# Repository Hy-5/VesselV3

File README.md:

# Vessel (rev 1.0)

*ISO-FR 75-ish keyboard with I2C OLED, RGB (WS2812B-2020) and rotary encoder*

* Keyboard Maintainer: [Hy-5 (Ismael Coulibaly)](https://github.com/Hy-5)
* Hardware Supported: *STM32F446RET6TR*

[WIP]

Make example for this keyboard (after setting up your build environment):

    qmk compile -kb vessel -km base 2>&1 | ts '%Y-%m-%d %H:%M:%S

Flashing example for this keyboard:

    A - Initial flashing
        1 - Bridge "boot0 to 3v3_1" solder jumper to pull boot0 high
        2 - Desolder logic level shifter to keep boot1 pin low
        3 - Plug in the keyboard, it will boot in dfu bootloader mode
        4 - Use whatever program you prefer, QMK Toolbox, STM32 Programmer, STLink V2 etc.
    B - After initial flashing
        1 - Keep M12 button (row0, col11) pressed while plugging in the keyboard to launch in bootloader mode
        2 - Use QMK Toolbox for flashing

See the [build environment setup](https://docs.qmk.fm/#/getting_started_build_tools) and the [make instructions](https://docs.qmk.fm/#/getting_started_make_guide) for more information. Brand new to QMK? Start with our [Complete Newbs Guide](https://docs.qmk.fm/#/newbs).

## Bootloader

Enter the bootloader in 1 way:

* **Bootmagic reset**: Hold down the M12 key at ((row0, col11) in the matrix) and plug in the keyboard

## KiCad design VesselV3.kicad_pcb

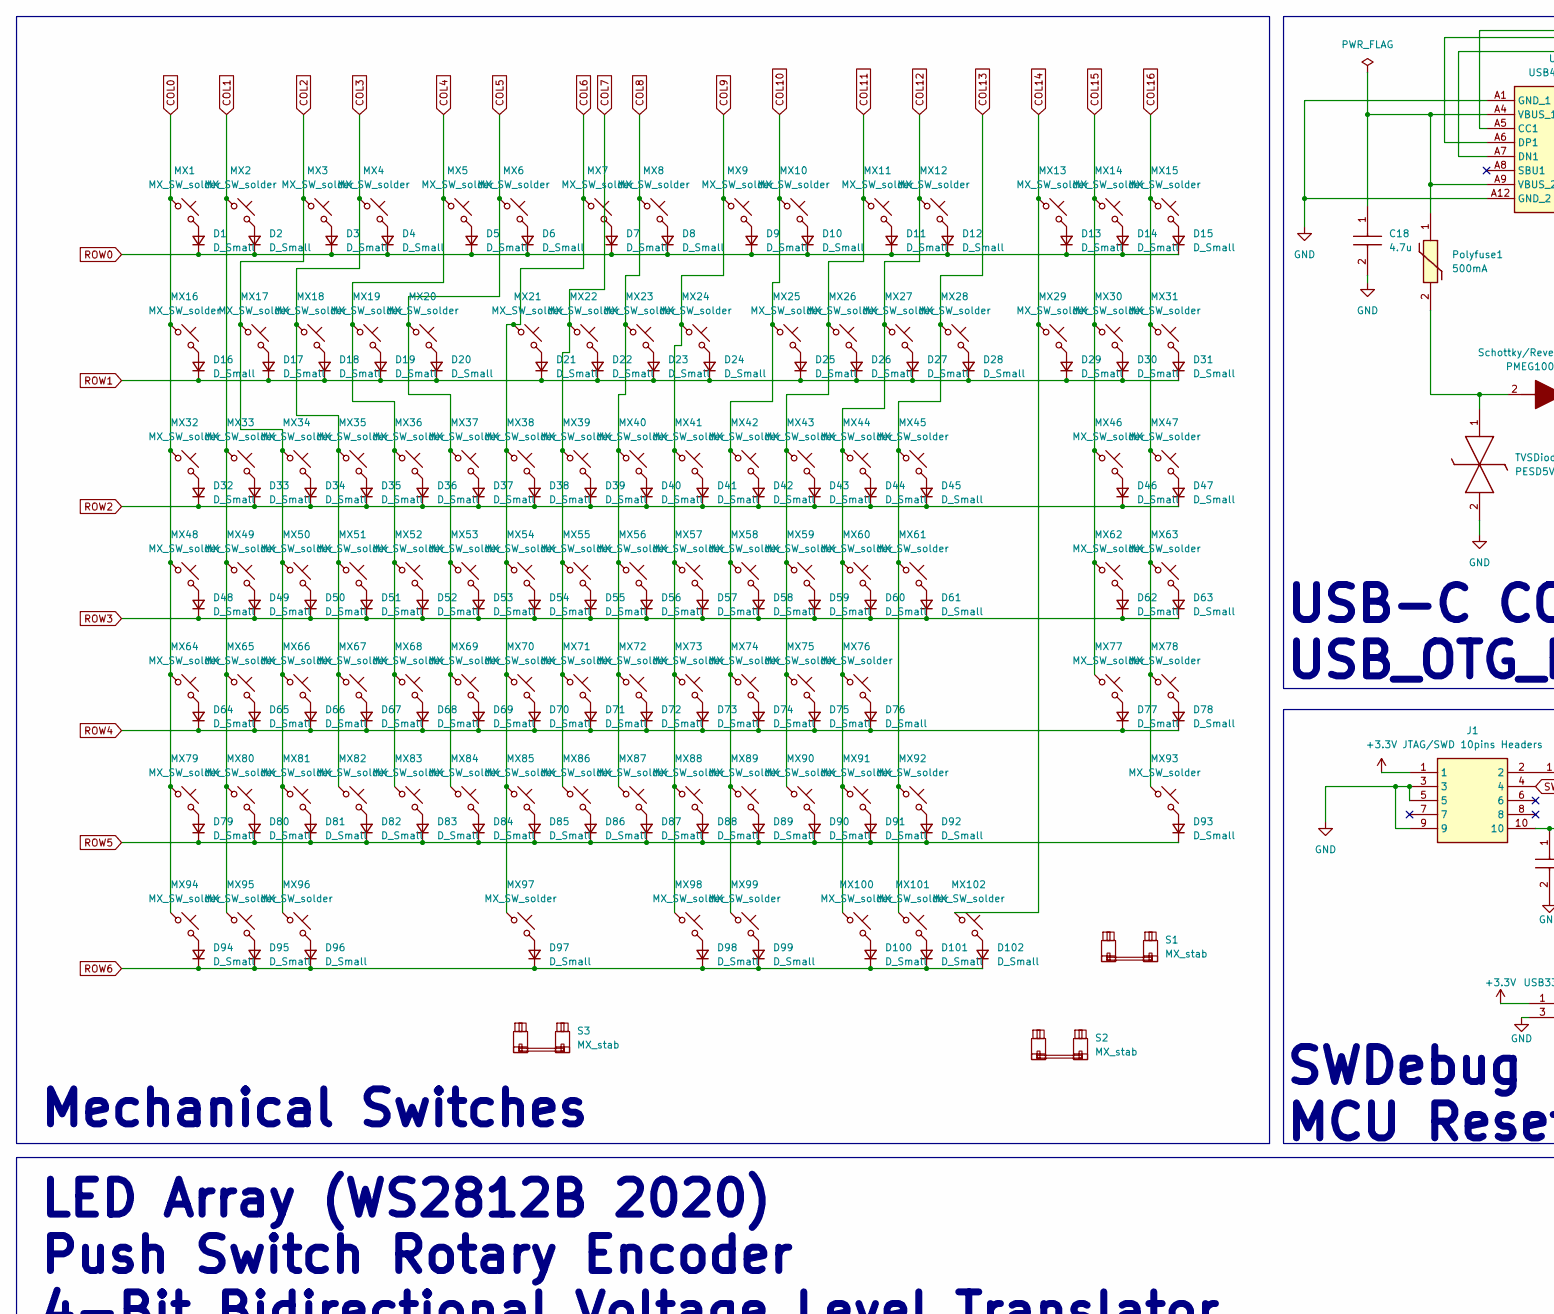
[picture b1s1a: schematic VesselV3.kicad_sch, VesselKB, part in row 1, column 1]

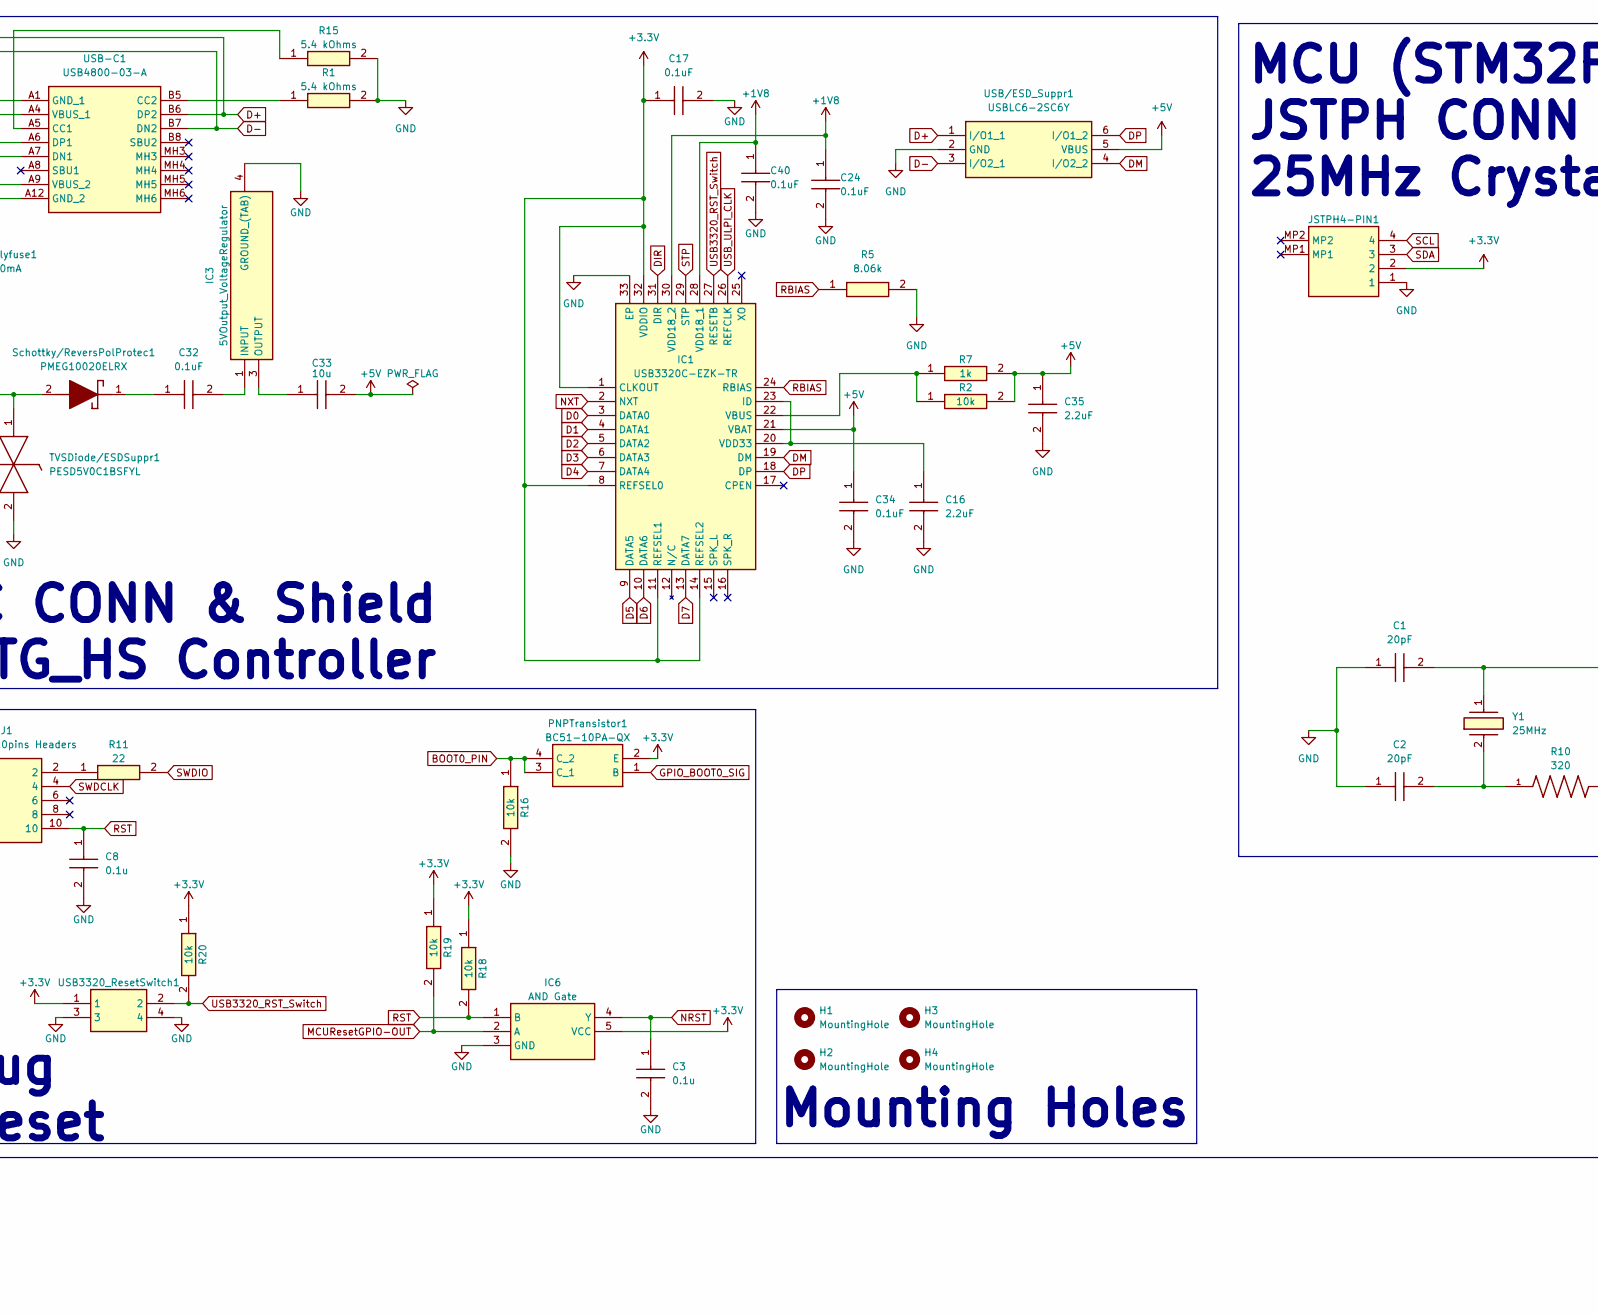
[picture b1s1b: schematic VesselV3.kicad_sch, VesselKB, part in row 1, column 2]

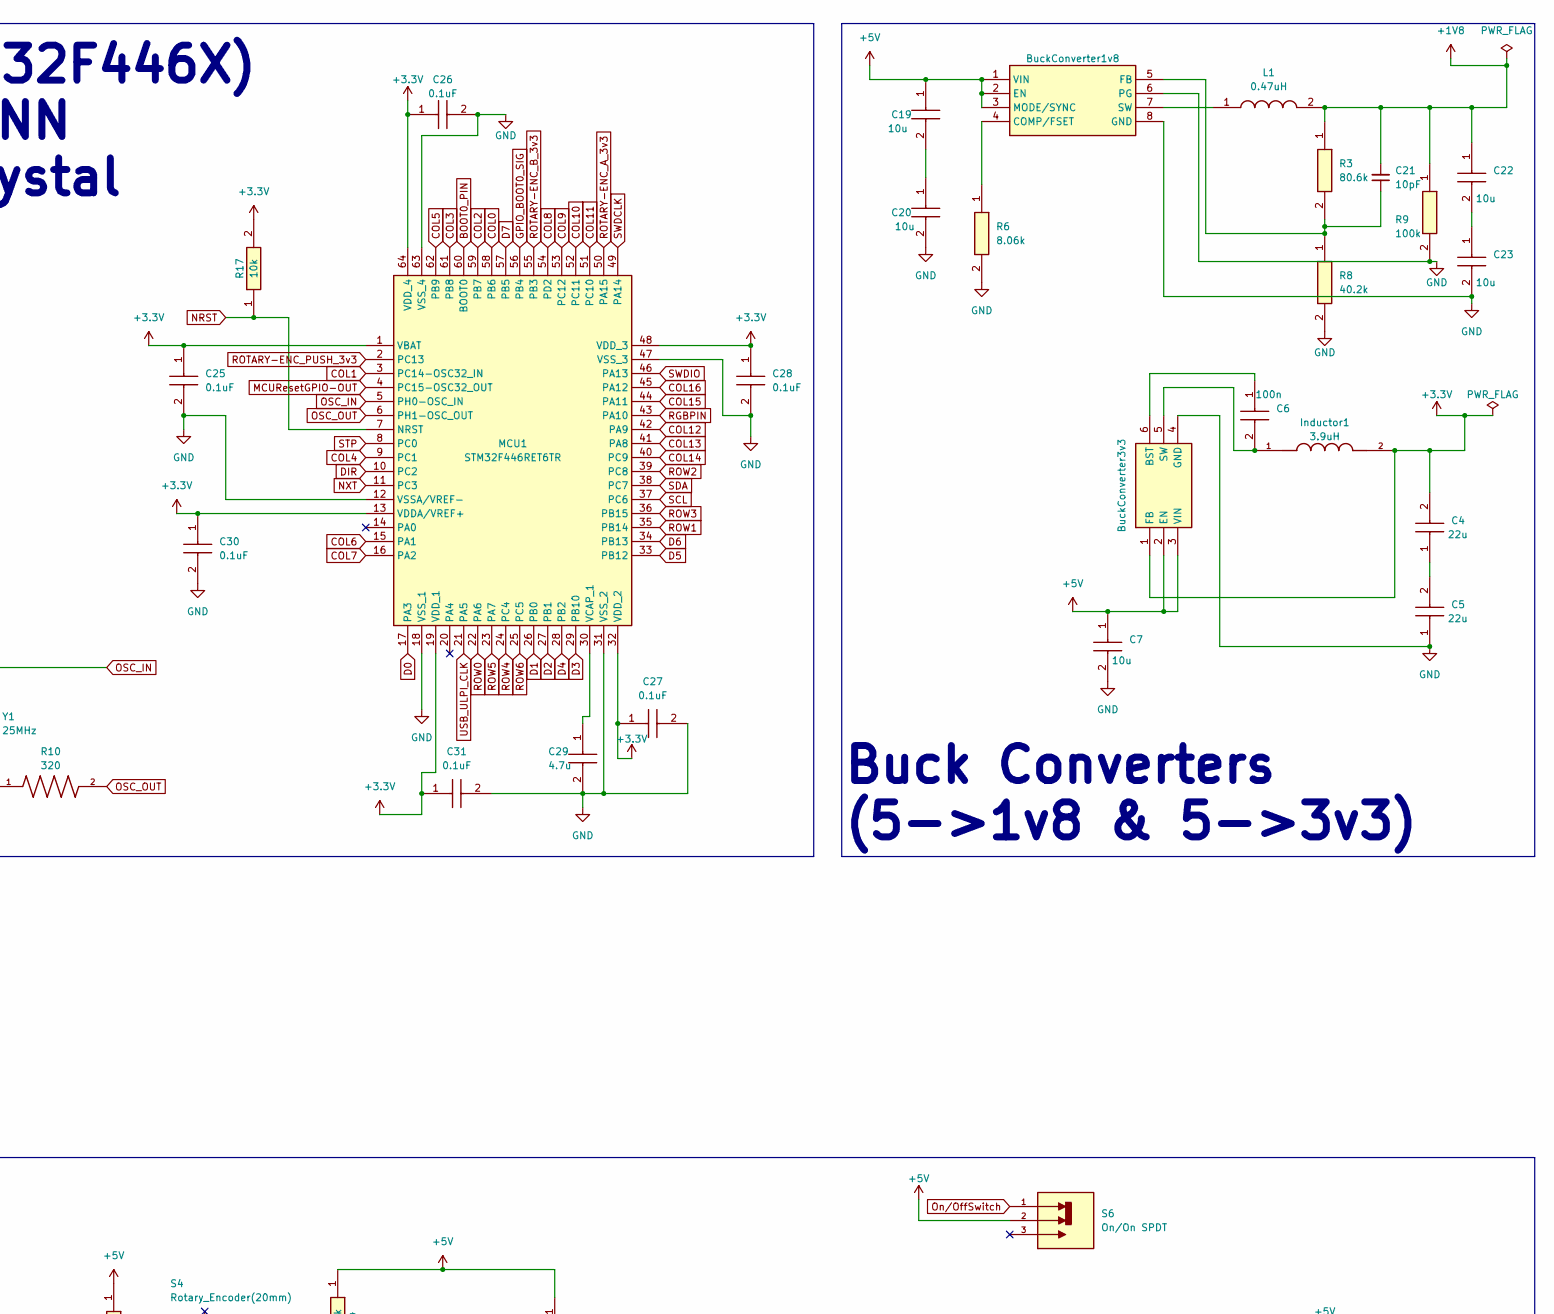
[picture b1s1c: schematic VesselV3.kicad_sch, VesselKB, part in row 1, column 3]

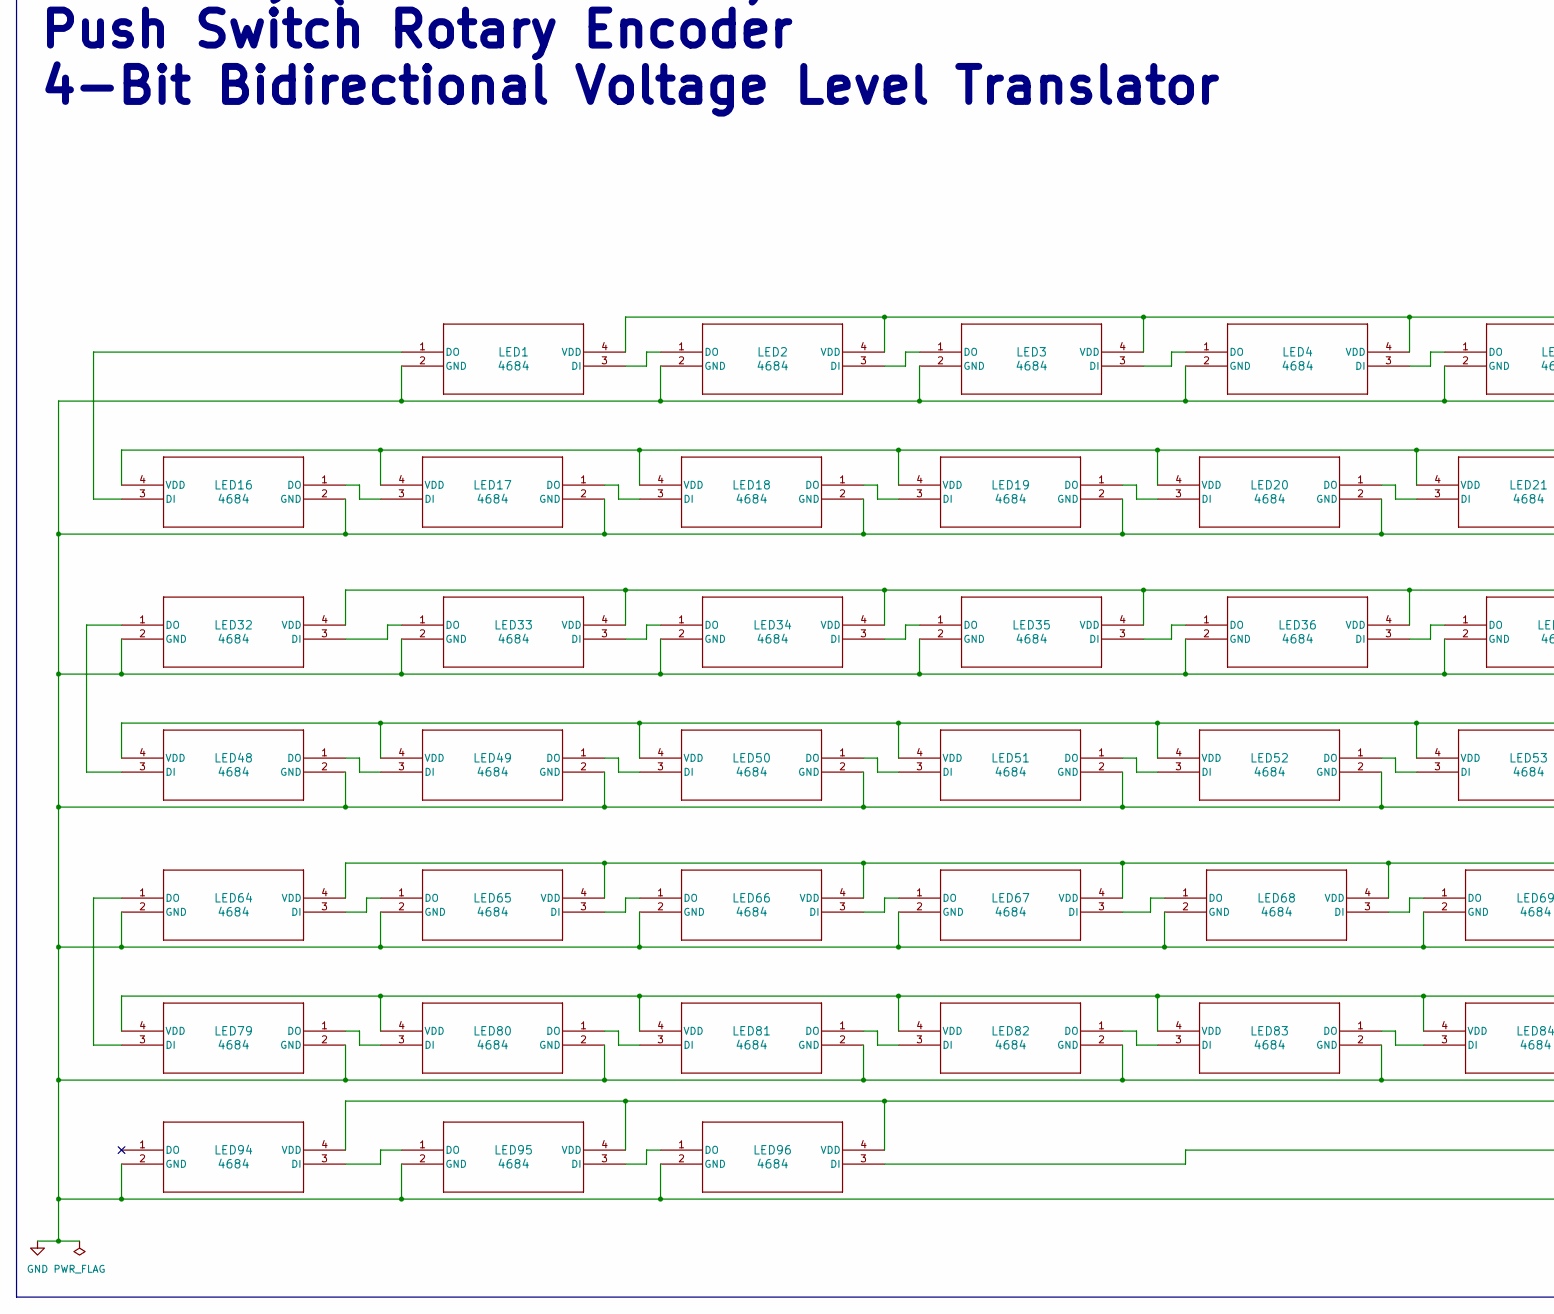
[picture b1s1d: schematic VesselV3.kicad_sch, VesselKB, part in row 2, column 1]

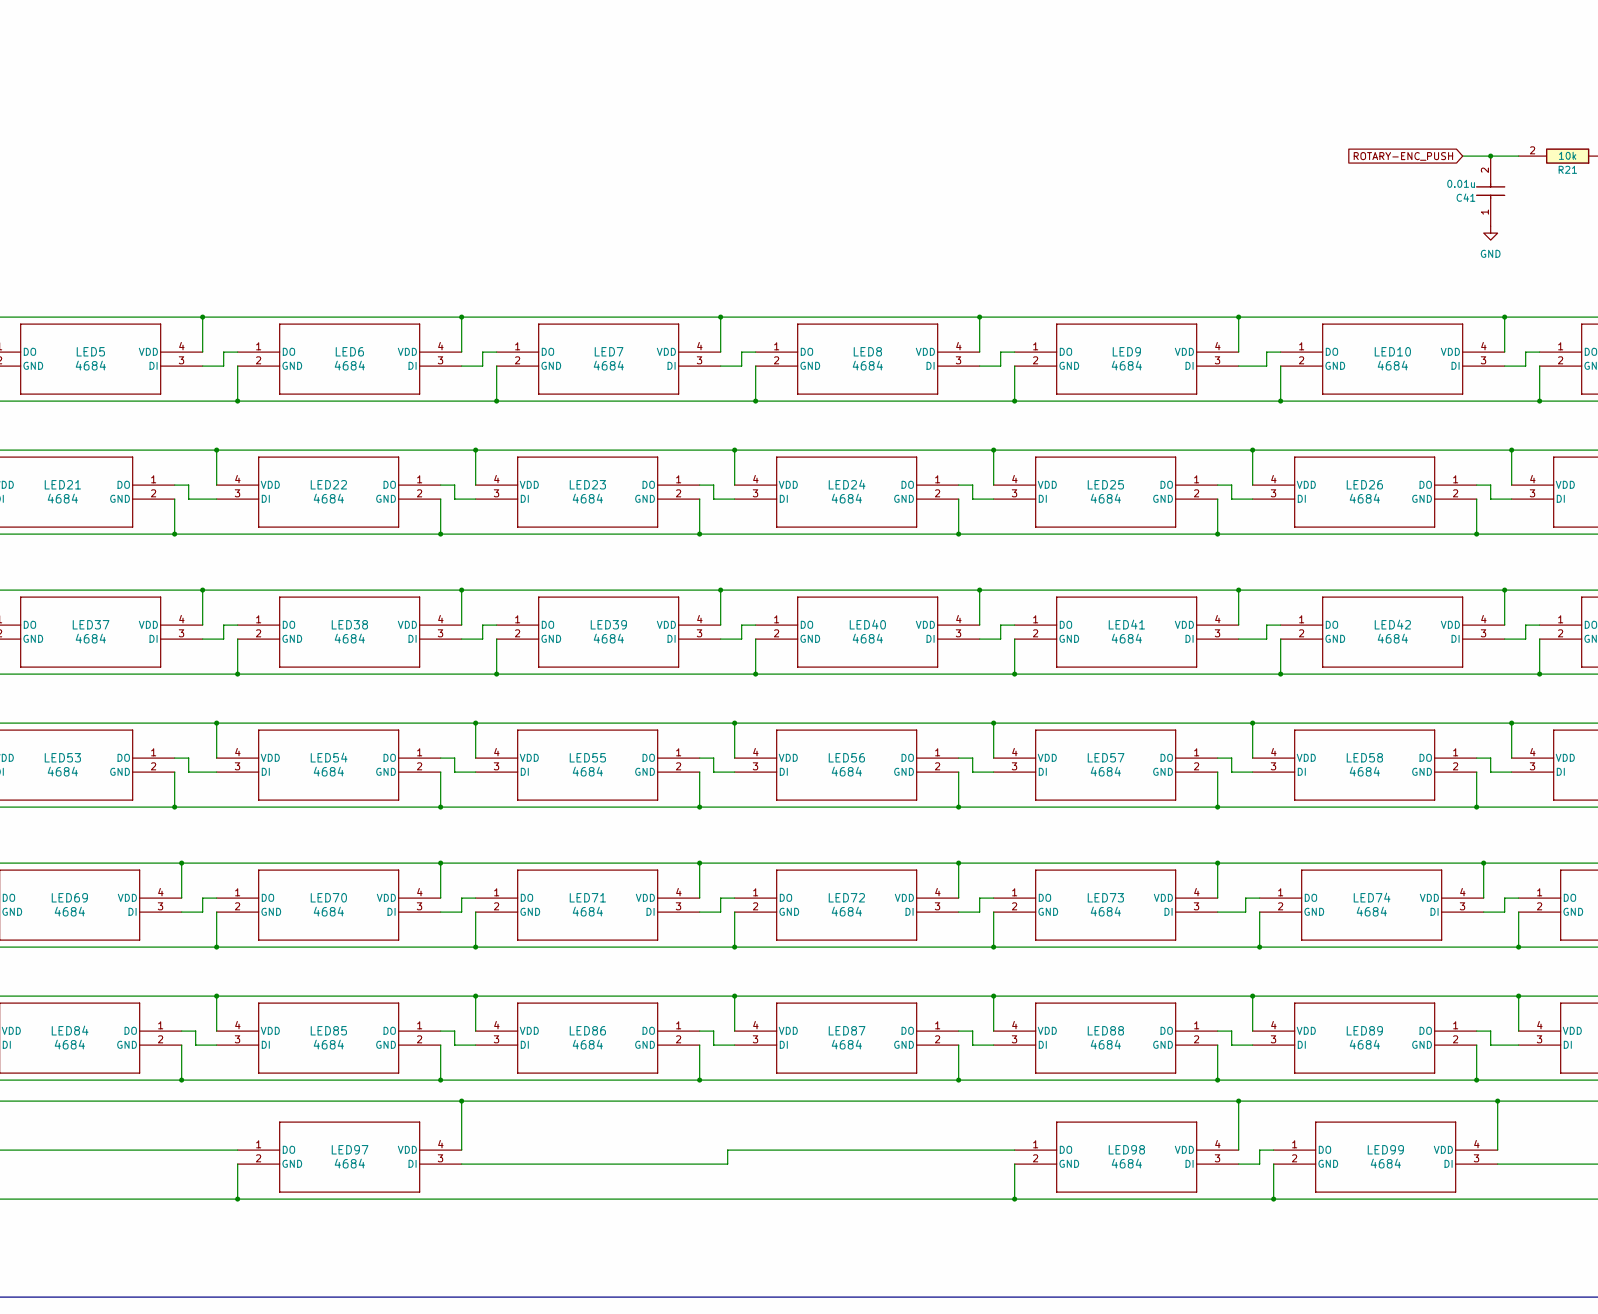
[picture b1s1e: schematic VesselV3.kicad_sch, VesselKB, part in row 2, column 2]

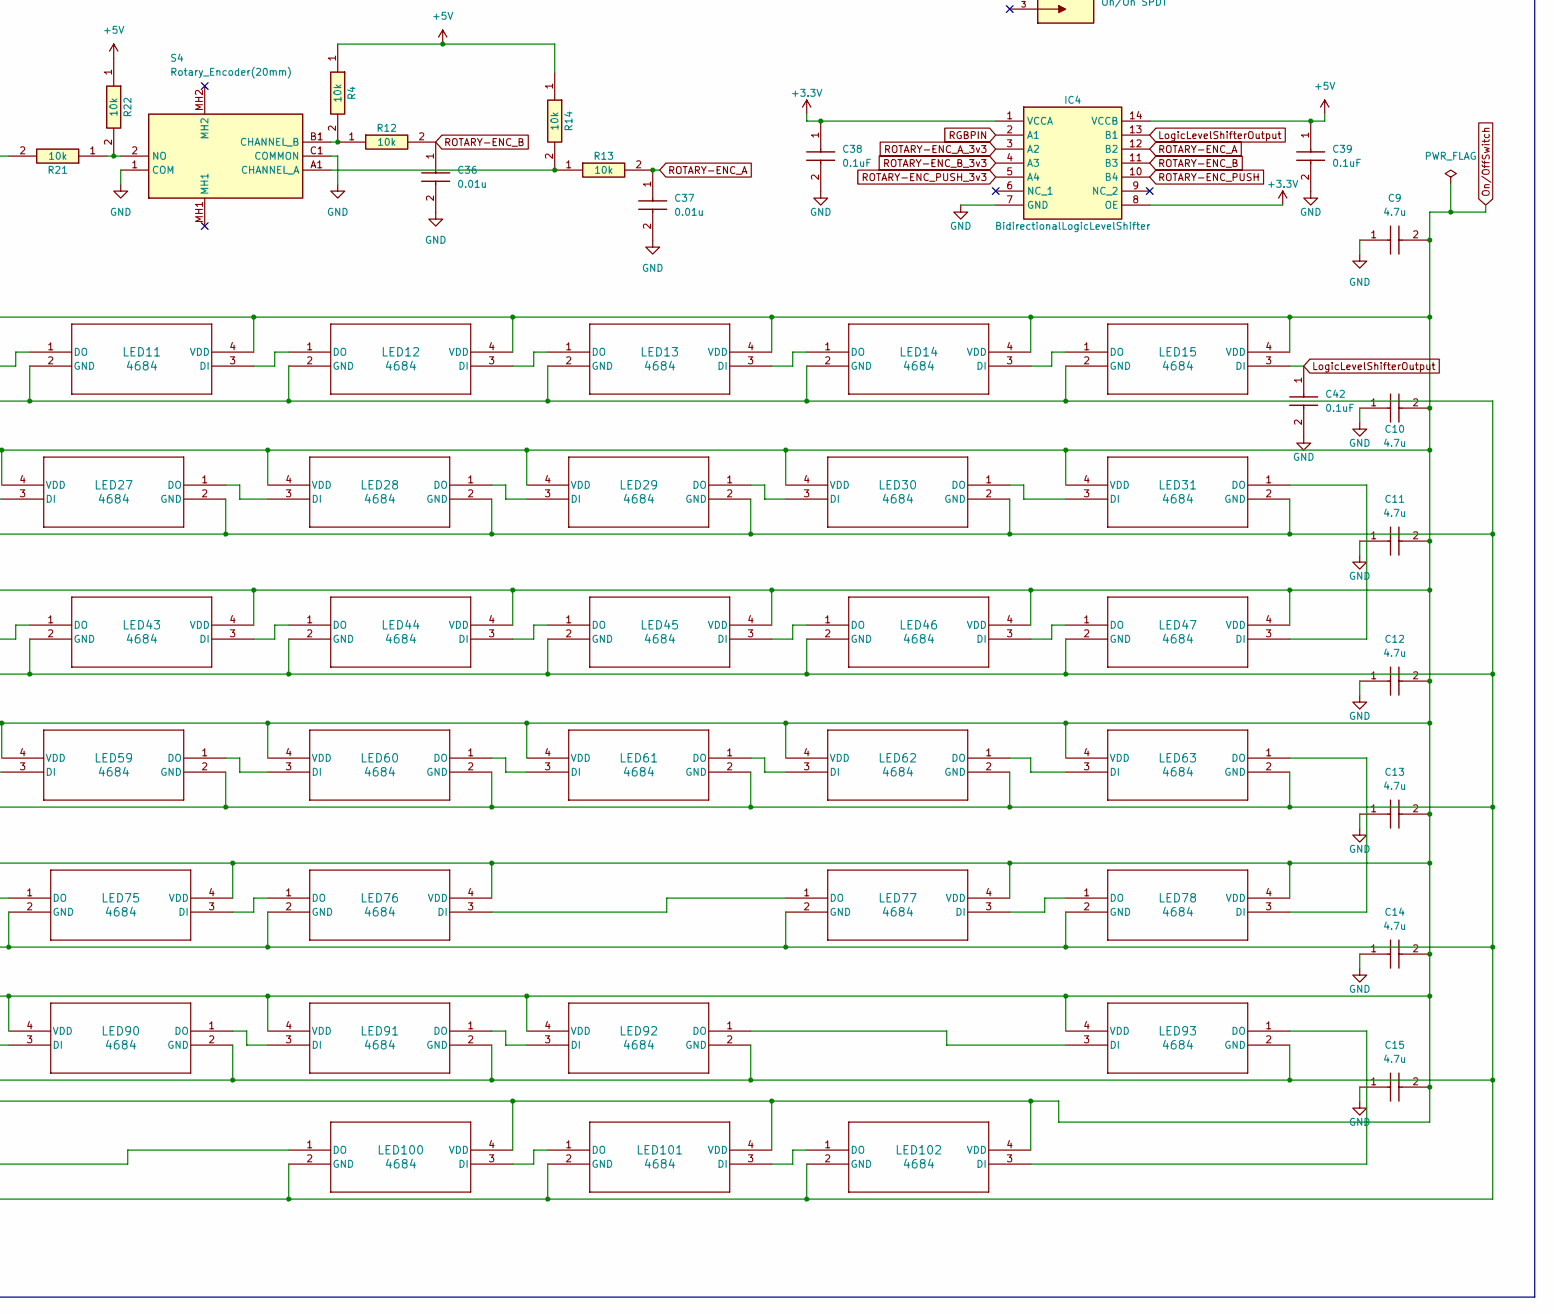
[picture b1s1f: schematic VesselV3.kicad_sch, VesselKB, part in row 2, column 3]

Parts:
BuckConverter1v8: TPS6285010MQDRLRQ1; SOTFL50P160X60-8N; Mouser Part Number 595-S6285010MQDRLRQ1
BuckConverter3v3: AP63203WU-7; SOT95P280X100-6N; Mouser Part Number 621-AP63203WU-7
C1, C2: 20pF; C0603; Mouser Part Number 80-C0603C200G8HACTU
C3, C8: 0.1u; C0805; Mouser Part Number 80-C0805C104J8R
C4, C5: c=2.2e-05; CAPC2012X95N; Mouser Part Number 187-CL21A226KQCLRNC
C6: c=1e-07; CAPC2012X95N; Mouser Part Number 187-CL21B104KBCNNNC
C7, C19, C20, C22, C23, C33: c=1e-05; CAPC2012X140N; Mouser Part Number 187-CL21A106KOQNNNE
C9, C10, C11, C12, C13, C14, C15, C18, C29: 4.7u; C0805; Mouser Part Number 80-C0805C475J8RAUTO
C16, C35: 2.2uF; CAPC1608X90N; Mouser Part Number 187-CL10B225KP8NNNC
C17, C24, C25, C26, C27, C28, C30, C31, C32, C34, C38, C39, C40, C42: 0.1uF; CAPC1005X55N; Mouser Part Number 81-GRM155R71A104JA1D
C21: 10pF; CAPC2012X75N; Manufacturer_Part_Number CL21C100CBANNNC; DigikeyPartNumber 1276-2561-2-ND
C36, C37, C41: 0.01u; CAPC1005X56N; Mouser Part Number 581-0402ZC103JAT2A
D1, D2, D3, D4, D5, D6, D7, D8, D9, D10, D11, D12, D13, D14, D15, D16, D17, D18, D19, D20, D21, D22, D23, D24, D25, D26, D27, D28, D29, D30, D31, D32, D33, D34, D35, D36, D37, D38, D39, D40, D41, D42, D43, D44, D45, D46, D47, D48, D49, D50, D51, D52, D53, D54, D55, D56, D57, D58, D59, D60, D61, D62, D63, D64, D65, D66, D67, D68, D69, D70, D71, D72, D73, D74, D75, D76, D77, D78, D79, D80, D81, D82, D83, D84, D85, D86, D87, D88, D89, D90, D91, D92, D93, D94, D95, D96, D97, D98, D99, D100, D101, D102: D_Small; SODFL3816X120N; Manufacturer_Part_Number 1N4148W; DigikeyPartNumber 4878-1N4148WTR-ND
H1, H2, H3, H4: MountingHole; MountingHole_2.5mm_Pad_TopBottom
IC1: USB3320C-EZK-TR; QFN50P500X500X100-33N-D; Mouser Part Number 886-USB3320C-EZK-TR
IC3: 5VOutput_VoltageRegulator; TO228P972X240-3N; Mouser Part Number 511-LF50ABDT-TR
IC4: BidirectionalLogicLevelShifter; SOP65P640X120-14N; Mouser Part Number 595-TXB0104PWR
IC6: AND Gate; SOT65P212X110-5N; Mouser Part Number 771-74AUP1G09GWQ100H
Inductor1: 3.9uH; IND_LQH32NH3R9J23L; PARTREV N/A; Mouser Part Number 81-LQH32NH3R9J23L
J1: JTAG/SWD 10pins Headers; HUSSP10W40P127_2X5_635X340X420P; Mouser Part Number 855-M50-3600542R
JSTPH4-PIN1: 4392; Mouser Part Number 485-4392
L1: 0.47uH; INDC2012X105N; Mouser Part Number 810-MLZ2012DR47DT000
LED1, LED2, LED3, LED4, LED5, LED6, LED7, LED8, LED9, LED10, LED11, LED12, LED13, LED14, LED15, LED16, LED17, LED18, LED19, LED20, LED21, LED22, LED23, LED24, LED25, LED26, LED27, LED28, LED29, LED30, LED31, LED32, LED33, LED34, LED35, LED36, LED37, LED38, LED39, LED40, LED41, LED42, LED43, LED44, LED45, LED46, LED47, LED48, LED49, LED50, LED51, LED52, LED53, LED54, LED55, LED56, LED57, LED58, LED59, LED60, LED61, LED62, LED63, LED64, LED65, LED66, LED67, LED68, LED69, LED70, LED71, LED72, LED73, LED74, LED75, LED76, LED77, LED78, LED79, LED80, LED81, LED82, LED83, LED84, LED85, LED86, LED87, LED88, LED89, LED90, LED91, LED92, LED93, LED94, LED95, LED96, LED97, LED98, LED99, LED100, LED101, LED102: 4684; 4684_ADA; Manufacturer_Part_Number 4684; DigikeyPartNumber 1528-4684-ND
MCU1: STM32F446RET6TR; QFP50P1200X1200X160-64N; Mouser Part Number 511-STM32F446RET6TR
MX1, MX2, MX3, MX4, MX5, MX6, MX7, MX8, MX9, MX10, MX11, MX12, MX13, MX14, MX15, MX16, MX17, MX18, MX19, MX20, MX21, MX22, MX23, MX24, MX25, MX26, MX27, MX28, MX29, MX30, MX31, MX32, MX33, MX34, MX35, MX36, MX37, MX38, MX39, MX40, MX41, MX42, MX43, MX44, MX46, MX47, MX49, MX50, MX51, MX52, MX53, MX54, MX55, MX56, MX57, MX58, MX59, MX60, MX62, MX63, MX65, MX66, MX67, MX68, MX69, MX70, MX71, MX72, MX73, MX74, MX75, MX76, MX77, MX78, MX80, MX81, MX82, MX83, MX84, MX85, MX86, MX87, MX88, MX89, MX90, MX92, MX93, MX100, MX101, MX102: MX_SW_solder; SW_Cherry_MX_PCB_1.00u
MX45: MX_SW_solder; SW_Cherry_MX_PCB_2.00u
MX48: MX_SW_solder; SW_Cherry_MX_PCB_1.50u
MX61: MX_SW_solder; SW_Cherry_MX_PCB_ISOEnter
MX64, MX91: MX_SW_solder; SW_Cherry_MX_PCB_1.75u
MX79, MX94, MX95, MX96, MX98, MX99: MX_SW_solder; SW_Cherry_MX_PCB_1.25u
MX97: MX_SW_solder; SW_Cherry_MX_PCB_6.25u
PNPTransistor1: BC51-10PA-QX; BC55PASQX; Mouser Part Number 771-BC51-10PA-QX
Polyfuse1: 500mA; 1206L05015YR; Mouser Part Number 576-1206L050/15YR
R1, R15: 5.4 kOhms; RESC1005X40N; Mouser Part Number 755-ESR01MZPF5101
R2, R4, R12, R13, R14, R16, R17, R18, R19, R20, R21, R22: 10k; RESC2012X50N; Mouser Part Number 71-CRCW080510K0JNEC
R3: 80.6k; RESC2012X60N; Mouser Part Number 652-CR0805FX-8062ELF
R5, R6: 8.06k; RESC2012X60N; Mouser Part Number 660-RK73H2ATTD8061F
R7: 1k; RESC5025X65N; Mouser Part Number 652-CRS2010FX1001ELF
R8: 40.2k; ERJ6ENF1000V; Mouser Part Number 667-ERJ-6ENF4022V
R9: 100k; RESC2012X60N; Mouser Part Number 603-RC0805FR-07100KL
R10: 320; RESC1005X40N; Manufacturer_Part_Number RN73H1ETTP3200D25; DigikeyPartNumber 2019-RN73H1ETTP3200D25TR-ND
R11: 22; RESC2012X50N; Mouser Part Number 71-CRCW0805-22-E3
S1, S2: MX_stab; Stabilizer_Cherry_MX_2.00u
S3: MX_stab; Stabilizer_Cherry_MX_6.25u
S4: Rotary_Encoder(20mm); PEC12R3220FS0024; Mouser Part Number 652-PEC12R3220FS0024
S6: On/On SPDT; SW_L102021ML04Q; PARTREV N/A; DigikeyPartNumber CKC5102-ND
Schottky/ReversPolProtec1: PMEG10020ELRX; SODFL3517X110N; Mouser Part Number 771-PMEG10020ELRX
TVSDiode/ESDSuppr1: PESD5V0C1BSFYL; PMEG3005AESFYL; Mouser Part Number 771-PESD5V0C1BSFYL
USB3320_ResetSwitch1: SKQGABE010; SKQGAKE010; Mouser Part Number 688-SKQGAB
USB-C1: USB4800-03-A; USB480003A; Mouser Part Number 640-USB4800-03-A
USB/ESD_Suppr1: USBLC6-2SC6Y; SOT95P280X145-6N; Mouser Part Number 511-USBLC6-2SC6Y
Y1: 25MHz; ATS25ASM1E; Mouser Part Number 774-ATS25ASM-1E

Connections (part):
+1V8: C21.2, C22.1, C24.1, C40.1, IC1.28 (VDD18_1), IC1.30 (VDD18_2), L1.2, R3.1, R9.1
+3.3V: BuckConverter3v3.1 (FB), C4.2, C17.1, C25.1, C26.1, C27.1, C28.1, C30.1, C31.1, C38.1, IC1.1 (CLKOUT), IC1.8 (REFSEL0), IC1.11 (REFSEL1), IC1.14 (REFSEL2), IC1.32 (VDDIO), IC4.1 (VCCA), IC4.8 (OE), IC6.5 (VCC), Inductor1.2, J1.1, JSTPH4-PIN1.2, MCU1.1 (VBAT), MCU1.13 (VDDA/VREF+), MCU1.19 (VDD_1), MCU1.32 (VDD_2), MCU1.48 (VDD_3), MCU1.64 (VDD_4), PNPTransistor1.2 (E), R17.2, R18.1, R19.1, R20.1, USB3320_ResetSwitch1.1
+5V: BuckConverter1v8.1 (VIN), BuckConverter1v8.2 (EN), BuckConverter1v8.3 (MODE/SYNC), BuckConverter3v3.2 (EN), BuckConverter3v3.3 (VIN), C7.1, C19.1, C33.2, C34.1, C35.1, C39.1, IC1.21 (VBAT), IC4.14 (VCCB), R2.2, R4.1, R7.2, R14.1, R22.1, S6.2, USB/ESD_Suppr1.5 (VBUS)
BOOT0_PIN: MCU1.60 (BOOT0), PNPTransistor1.3 (C_1), PNPTransistor1.4 (C_2), R16.1
COL0: MCU1.58 (PB6), MX1.1, MX16.1, MX32.1, MX48.1, MX64.1, MX79.1, MX94.1
COL1: MCU1.3 (PC14-OSC32_IN), MX2.1, MX33.1, MX49.1, MX65.1, MX80.1, MX95.1
COL2: MCU1.59 (PB7), MX3.1, MX17.1, MX34.1, MX50.1, MX66.1, MX81.1, MX96.1
COL3: MCU1.61 (PB8), MX4.1, MX18.1, MX35.1, MX51.1, MX67.1, MX82.1
COL4: MCU1.9 (PC1), MX5.1, MX19.1, MX36.1, MX52.1, MX68.1, MX83.1
COL5: MCU1.62 (PB9), MX6.1, MX20.1, MX37.1, MX53.1, MX69.1, MX84.1
COL6: MCU1.15 (PA1), MX7.1, MX21.1, MX38.1, MX54.1, MX70.1, MX85.1, MX97.1
COL7: MCU1.16 (PA2), MX22.1, MX39.1, MX55.1, MX71.1, MX86.1
COL8: MCU1.54 (PD2), MX8.1, MX23.1, MX40.1, MX56.1, MX72.1, MX87.1
COL9: MCU1.53 (PC12), MX9.1, MX24.1, MX41.1, MX57.1, MX73.1, MX88.1, MX98.1
COL10: MCU1.52 (PC11), MX10.1, MX25.1, MX42.1, MX58.1, MX74.1, MX89.1, MX99.1
COL11: MCU1.51 (PC10), MX11.1, MX26.1, MX43.1, MX59.1, MX75.1, MX90.1
COL12: MCU1.42 (PA9), MX12.1, MX27.1, MX44.1, MX60.1, MX76.1, MX91.1, MX100.1
COL13: MCU1.41 (PA8), MX28.1, MX45.1, MX61.1, MX92.1, MX101.1
COL14: MCU1.40 (PC9), MX13.1, MX29.1, MX102.1
COL15: MCU1.44 (PA11), MX14.1, MX30.1, MX46.1, MX62.1, MX77.1
COL16: MCU1.45 (PA12), MX15.1, MX31.1, MX47.1, MX63.1, MX78.1, MX93.1
D0: IC1.3 (DATA0), MCU1.17 (PA3)
D1: IC1.4 (DATA1), MCU1.26 (PB0)
D2: IC1.5 (DATA2), MCU1.27 (PB1)
D3: IC1.6 (DATA3), MCU1.29 (PB10)
D4: IC1.7 (DATA4), MCU1.28 (PB2)
D5: IC1.9 (DATA5), MCU1.33 (PB12)
D6: IC1.10 (DATA6), MCU1.34 (PB13)
D7: IC1.13 (DATA7), MCU1.57 (PB5)
D+: USB-C1.A6 (DP1), USB-C1.B6 (DP2), USB/ESD_Suppr1.1 (I/O1_1)
D-: USB-C1.A7 (DN1), USB-C1.B7 (DN2), USB/ESD_Suppr1.3 (I/O2_1)
DIR: IC1.31 (DIR), MCU1.10 (PC2)
DM: IC1.19 (DM), USB/ESD_Suppr1.4 (I/O2_2)
DP: IC1.18 (DP), USB/ESD_Suppr1.6 (I/O1_2)
GND: BuckConverter1v8.6 (PG), BuckConverter1v8.8 (GND), BuckConverter3v3.4 (GND), C1.1, C2.1, C3.2, C5.1, C7.2, C8.2, C9.1, C10.1, C11.1, C12.1, C13.1, C14.1, C15.1, C16.2, C17.2, C18.2, C20.2, C23.2, C24.2, C25.2, C26.2, C27.2, C28.2, C29.2, C30.2, C31.2, C34.2, C35.2, C36.2, C37.2, C38.2, C39.2, C40.2, C41.1, C42.2, IC1.33 (EP), IC3.4 (GROUND_(TAB)), IC4.7 (GND), IC6.3 (GND), J1.3, J1.5, J1.9, JSTPH4-PIN1.1, LED1.2 (GND), LED2.2 (GND), LED3.2 (GND), LED4.2 (GND), LED5.2 (GND), LED6.2 (GND), LED7.2 (GND), LED8.2 (GND), LED9.2 (GND), LED10.2 (GND), LED11.2 (GND), LED12.2 (GND), LED13.2 (GND), LED14.2 (GND), LED15.2 (GND), LED16.2 (GND), LED17.2 (GND), LED18.2 (GND), LED19.2 (GND), LED20.2 (GND), LED21.2 (GND), LED22.2 (GND), LED23.2 (GND), LED24.2 (GND), LED25.2 (GND), LED26.2 (GND), LED27.2 (GND), LED28.2 (GND), LED29.2 (GND), LED30.2 (GND), LED31.2 (GND), LED32.2 (GND), LED33.2 (GND), LED34.2 (GND), LED35.2 (GND), LED36.2 (GND), LED37.2 (GND), LED38.2 (GND), LED39.2 (GND), LED40.2 (GND)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
GPIO_BOOT0_SIG: MCU1.56 (PB4), PNPTransistor1.1 (B)
LogicLevelShifterOutput: C42.1, IC4.13 (B1), LED15.3 (DI)
MCUResetGPIO-OUT: IC6.2 (A), MCU1.4 (PC15-OSC32_OUT), R19.2
NRST: C3.1, IC6.4 (Y), MCU1.7 (NRST), R17.1
NXT: IC1.2 (NXT), MCU1.11 (PC3)
unnamed: BuckConverter1v8.4 (COMP/FSET), R6.1
unnamed: BuckConverter1v8.5 (FB), C21.1, R3.2, R8.1
unnamed: BuckConverter1v8.7 (SW), L1.1
unnamed: BuckConverter3v3.6 (BST), C6.1
unnamed: BuckConverter3v3.5 (SW), C6.2, Inductor1.1
unnamed: C4.1, C5.2
unnamed: C19.2, C20.1
unnamed: C22.2, C23.1
unnamed: D1.2 (A), MX1.2
unnamed: D2.2 (A), MX2.2
unnamed: D3.2 (A), MX3.2
unnamed: D4.2 (A), MX4.2
unnamed: D5.2 (A), MX5.2
unnamed: D6.2 (A), MX6.2
unnamed: D7.2 (A), MX7.2
unnamed: D8.2 (A), MX8.2
unnamed: D9.2 (A), MX9.2
unnamed: D10.2 (A), MX10.2
unnamed: D11.2 (A), MX11.2
unnamed: D12.2 (A), MX12.2
unnamed: D13.2 (A), MX13.2
unnamed: D14.2 (A), MX14.2
unnamed: D15.2 (A), MX15.2
unnamed: D16.2 (A), MX16.2
unnamed: D17.2 (A), MX17.2
unnamed: D18.2 (A), MX18.2
unnamed: D19.2 (A), MX19.2
unnamed: D20.2 (A), MX20.2
unnamed: D21.2 (A), MX21.2
unnamed: D22.2 (A), MX22.2
unnamed: D23.2 (A), MX23.2
unnamed: D24.2 (A), MX24.2
unnamed: D25.2 (A), MX25.2
unnamed: D26.2 (A), MX26.2
unnamed: D27.2 (A), MX27.2
unnamed: D28.2 (A), MX28.2
unnamed: D29.2 (A), MX29.2
unnamed: D30.2 (A), MX30.2
unnamed: D31.2 (A), MX31.2
unnamed: D32.2 (A), MX32.2
unnamed: D33.2 (A), MX33.2
unnamed: D34.2 (A), MX34.2
unnamed: D35.2 (A), MX35.2
unnamed: D36.2 (A), MX36.2
unnamed: D37.2 (A), MX37.2
unnamed: D38.2 (A), MX38.2
unnamed: D39.2 (A), MX39.2
unnamed: D40.2 (A), MX40.2
unnamed: D41.2 (A), MX41.2
unnamed: D42.2 (A), MX42.2
unnamed: D43.2 (A), MX43.2
unnamed: D44.2 (A), MX44.2
unnamed: D45.2 (A), MX45.2
unnamed: D46.2 (A), MX46.2
unnamed: D47.2 (A), MX47.2
unnamed: D48.2 (A), MX48.2
unnamed: D49.2 (A), MX49.2
unnamed: D50.2 (A), MX50.2
unnamed: D51.2 (A), MX51.2
unnamed: D52.2 (A), MX52.2
unnamed: D53.2 (A), MX53.2
unnamed: D54.2 (A), MX54.2
unnamed: D55.2 (A), MX55.2
unnamed: D56.2 (A), MX56.2
unnamed: D57.2 (A), MX57.2
unnamed: D58.2 (A), MX58.2
unnamed: D59.2 (A), MX59.2
unnamed: D60.2 (A), MX60.2
unnamed: D61.2 (A), MX61.2
unnamed: D62.2 (A), MX62.2
unnamed: D63.2 (A), MX63.2
unnamed: D64.2 (A), MX64.2
unnamed: D65.2 (A), MX65.2
unnamed: D66.2 (A), MX66.2
unnamed: D67.2 (A), MX67.2
unnamed: D68.2 (A), MX68.2
unnamed: D69.2 (A), MX69.2
unnamed: D70.2 (A), MX70.2
unnamed: D71.2 (A), MX71.2
unnamed: D72.2 (A), MX72.2
unnamed: D73.2 (A), MX73.2
unnamed: D74.2 (A), MX74.2
unnamed: D75.2 (A), MX75.2
unnamed: D76.2 (A), MX76.2
unnamed: D77.2 (A), MX77.2
unnamed: D78.2 (A), MX78.2
unnamed: D79.2 (A), MX79.2
unnamed: D80.2 (A), MX80.2
unnamed: D81.2 (A), MX81.2
unnamed: D82.2 (A), MX82.2
unnamed: D83.2 (A), MX83.2
unnamed: D84.2 (A), MX84.2
unnamed: D85.2 (A), MX85.2
unnamed: D86.2 (A), MX86.2
unnamed: D87.2 (A), MX87.2
unnamed: D88.2 (A), MX88.2
unnamed: D89.2 (A), MX89.2
unnamed: D90.2 (A), MX90.2
unnamed: D91.2 (A), MX91.2
unnamed: D92.2 (A), MX92.2
unnamed: D93.2 (A), MX93.2
unnamed: D94.2 (A), MX94.2
unnamed: D95.2 (A), MX95.2
unnamed: D96.2 (A), MX96.2
unnamed: D97.2 (A), MX97.2
unnamed: D98.2 (A), MX98.2
unnamed: D99.2 (A), MX99.2
unnamed: D100.2 (A), MX100.2
unnamed: D101.2 (A), MX101.2
unnamed: D102.2 (A), MX102.2
unnamed: C16.1, IC1.20 (VDD33), IC1.23 (ID)
unnamed: IC1.22 (VBUS), R2.1, R7.1
unnamed: C32.2, IC3.1 (INPUT)
unnamed: C33.1, IC3.3 (OUTPUT)
unnamed: J1.2, R11.1
unnamed: LED1.3 (DI), LED2.1 (DO)
unnamed: LED1.1 (DO), LED16.3 (DI)
unnamed: LED2.3 (DI), LED3.1 (DO)
unnamed: LED3.3 (DI), LED4.1 (DO)
unnamed: LED4.3 (DI), LED5.1 (DO)
unnamed: LED5.3 (DI), LED6.1 (DO)
unnamed: LED6.3 (DI), LED7.1 (DO)
unnamed: LED7.3 (DI), LED8.1 (DO)
unnamed: LED8.3 (DI), LED9.1 (DO)
unnamed: LED10.3 (DI), LED11.1 (DO)
unnamed: LED9.3 (DI), LED10.1 (DO)
unnamed: LED11.3 (DI), LED12.1 (DO)
unnamed: LED12.3 (DI), LED13.1 (DO)
unnamed: LED13.3 (DI), LED14.1 (DO)
unnamed: LED14.3 (DI), LED15.1 (DO)
unnamed: LED16.1 (DO), LED17.3 (DI)
unnamed: LED17.1 (DO), LED18.3 (DI)
unnamed: LED18.1 (DO), LED19.3 (DI)
unnamed: LED19.1 (DO), LED20.3 (DI)
unnamed: LED20.1 (DO), LED21.3 (DI)
unnamed: LED21.1 (DO), LED22.3 (DI)
unnamed: LED22.1 (DO), LED23.3 (DI)
unnamed: LED23.1 (DO), LED24.3 (DI)
unnamed: LED24.1 (DO), LED25.3 (DI)
unnamed: LED25.1 (DO), LED26.3 (DI)
unnamed: LED26.1 (DO), LED27.3 (DI)
unnamed: LED27.1 (DO), LED28.3 (DI)
unnamed: LED28.1 (DO), LED29.3 (DI)
unnamed: LED29.1 (DO), LED30.3 (DI)
unnamed: LED30.1 (DO), LED31.3 (DI)
unnamed: LED31.1 (DO), LED47.3 (DI)
unnamed: LED32.3 (DI), LED33.1 (DO)
unnamed: LED32.1 (DO), LED48.3 (DI)
unnamed: LED33.3 (DI), LED34.1 (DO)
unnamed: LED34.3 (DI), LED35.1 (DO)
unnamed: LED35.3 (DI), LED36.1 (DO)
unnamed: LED36.3 (DI), LED37.1 (DO)
unnamed: LED37.3 (DI), LED38.1 (DO)
unnamed: LED38.3 (DI), LED39.1 (DO)
unnamed: LED39.3 (DI), LED40.1 (DO)
unnamed: LED40.3 (DI), LED41.1 (DO)
unnamed: LED41.3 (DI), LED42.1 (DO)
unnamed: LED42.3 (DI), LED43.1 (DO)
unnamed: LED43.3 (DI), LED44.1 (DO)
unnamed: LED44.3 (DI), LED45.1 (DO)
unnamed: LED45.3 (DI), LED46.1 (DO)
unnamed: LED46.3 (DI), LED47.1 (DO)
unnamed: LED48.1 (DO), LED49.3 (DI)
unnamed: LED49.1 (DO), LED50.3 (DI)
unnamed: LED50.1 (DO), LED51.3 (DI)
unnamed: LED51.1 (DO), LED52.3 (DI)
unnamed: LED52.1 (DO), LED53.3 (DI)
unnamed: LED53.1 (DO), LED54.3 (DI)
unnamed: LED54.1 (DO), LED55.3 (DI)
unnamed: LED55.1 (DO), LED56.3 (DI)
unnamed: LED56.1 (DO), LED57.3 (DI)
unnamed: LED57.1 (DO), LED58.3 (DI)
unnamed: LED58.1 (DO), LED59.3 (DI)
unnamed: LED59.1 (DO), LED60.3 (DI)
unnamed: LED60.1 (DO), LED61.3 (DI)
unnamed: LED61.1 (DO), LED62.3 (DI)
unnamed: LED62.1 (DO), LED63.3 (DI)
unnamed: LED63.1 (DO), LED78.3 (DI)
unnamed: LED64.3 (DI), LED65.1 (DO)
unnamed: LED64.1 (DO), LED79.3 (DI)
unnamed: LED65.3 (DI), LED66.1 (DO)
unnamed: LED66.3 (DI), LED67.1 (DO)
unnamed: LED67.3 (DI), LED68.1 (DO)
unnamed: LED68.3 (DI), LED69.1 (DO)
unnamed: LED69.3 (DI), LED70.1 (DO)
unnamed: LED70.3 (DI), LED71.1 (DO)
unnamed: LED71.3 (DI), LED72.1 (DO)
unnamed: LED72.3 (DI), LED73.1 (DO)
unnamed: LED73.3 (DI), LED74.1 (DO)
unnamed: LED74.3 (DI), LED75.1 (DO)
unnamed: LED75.3 (DI), LED76.1 (DO)
unnamed: LED76.3 (DI), LED77.1 (DO)
unnamed: LED77.3 (DI), LED78.1 (DO)
unnamed: LED79.1 (DO), LED80.3 (DI)
unnamed: LED80.1 (DO), LED81.3 (DI)
unnamed: LED81.1 (DO), LED82.3 (DI)
unnamed: LED82.1 (DO), LED83.3 (DI)
unnamed: LED83.1 (DO), LED84.3 (DI)
unnamed: LED84.1 (DO), LED85.3 (DI)
unnamed: LED85.1 (DO), LED86.3 (DI)
unnamed: LED86.1 (DO), LED87.3 (DI)
unnamed: LED87.1 (DO), LED88.3 (DI)
unnamed: LED88.1 (DO), LED89.3 (DI)
unnamed: LED89.1 (DO), LED90.3 (DI)
unnamed: LED90.1 (DO), LED91.3 (DI)
unnamed: LED91.1 (DO), LED92.3 (DI)
unnamed: LED92.1 (DO), LED93.3 (DI)
unnamed: LED94.3 (DI), LED95.1 (DO)
unnamed: LED95.3 (DI), LED96.1 (DO)
unnamed: LED96.3 (DI), LED97.1 (DO)
unnamed: LED97.3 (DI), LED98.1 (DO)
unnamed: LED98.3 (DI), LED99.1 (DO)
unnamed: LED100.3 (DI), LED101.1 (DO)
unnamed: LED99.3 (DI), LED100.1 (DO)
unnamed: LED101.3 (DI), LED102.1 (DO)
unnamed: LED93.1 (DO), LED102.3 (DI)
unnamed: C29.1, MCU1.30 (VCAP_1)
unnamed: R13.1, R14.2, S4.A1 (CHANNEL_A)
unnamed: R4.2, R12.1, S4.B1 (CHANNEL_B)
unnamed: R21.1, R22.2, S4.2 (NO)
unnamed: Polyfuse1.2, Schottky/ReversPolProtec1.2 (A), TVSDiode/ESDSuppr1.1 (K1)
unnamed: C32.1, Schottky/ReversPolProtec1.1 (K)
unnamed: R15.1, USB-C1.A5 (CC1)
unnamed: R1.1, USB-C1.B5 (CC2)
unnamed: C18.1, Polyfuse1.1, USB-C1.A4 (VBUS_1), USB-C1.A9 (VBUS_2)
unnamed: C2.2, R10.1, Y1.2 (X2)
OSC_IN: C1.2, MCU1.5 (PH0-OSC_IN), Y1.1 (X1)
OSC_OUT: MCU1.6 (PH1-OSC_OUT), R10.2
On/OffSwitch: C9.2, C10.2, C11.2, C12.2, C13.2, C14.2, C15.2, LED1.4 (VDD), LED2.4 (VDD), LED3.4 (VDD), LED4.4 (VDD), LED5.4 (VDD), LED6.4 (VDD), LED7.4 (VDD), LED8.4 (VDD), LED9.4 (VDD), LED10.4 (VDD), LED11.4 (VDD), LED12.4 (VDD), LED13.4 (VDD), LED14.4 (VDD), LED15.4 (VDD), LED16.4 (VDD), LED17.4 (VDD), LED18.4 (VDD), LED19.4 (VDD), LED20.4 (VDD), LED21.4 (VDD), LED22.4 (VDD), LED23.4 (VDD), LED24.4 (VDD), LED25.4 (VDD), LED26.4 (VDD), LED27.4 (VDD), LED28.4 (VDD), LED29.4 (VDD), LED30.4 (VDD), LED31.4 (VDD), LED32.4 (VDD), LED33.4 (VDD), LED34.4 (VDD), LED35.4 (VDD), LED36.4 (VDD), LED37.4 (VDD), LED38.4 (VDD), LED39.4 (VDD), LED40.4 (VDD), LED41.4 (VDD), LED42.4 (VDD), LED43.4 (VDD), LED44.4 (VDD), LED45.4 (VDD), LED46.4 (VDD), LED47.4 (VDD), LED48.4 (VDD), LED49.4 (VDD), LED50.4 (VDD), LED51.4 (VDD), LED52.4 (VDD), LED53.4 (VDD), LED54.4 (VDD), LED55.4 (VDD), LED56.4 (VDD), LED57.4 (VDD), LED58.4 (VDD), LED59.4 (VDD), LED60.4 (VDD), LED61.4 (VDD), LED62.4 (VDD), LED63.4 (VDD), LED64.4 (VDD), LED65.4 (VDD), LED66.4 (VDD), LED67.4 (VDD), LED68.4 (VDD), LED69.4 (VDD), LED70.4 (VDD), LED71.4 (VDD), LED72.4 (VDD), LED73.4 (VDD), LED74.4 (VDD), LED75.4 (VDD), LED76.4 (VDD), LED77.4 (VDD), LED78.4 (VDD), LED79.4 (VDD)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
RBIAS: IC1.24 (RBIAS), R5.1
RGBPIN: IC4.2 (A1), MCU1.43 (PA10)
ROTARY-ENC_A: C37.1, IC4.12 (B2), R13.2
ROTARY-ENC_A_3v3: IC4.3 (A2), MCU1.50 (PA15)
ROTARY-ENC_B: C36.1, IC4.11 (B3), R12.2
ROTARY-ENC_B_3v3: IC4.4 (A3), MCU1.55 (PB3)
ROTARY-ENC_PUSH: C41.2, IC4.10 (B4), R21.2
ROTARY-ENC_PUSH_3v3: IC4.5 (A4), MCU1.2 (PC13)
ROW0: D1.1 (K), D2.1 (K), D3.1 (K), D4.1 (K), D5.1 (K), D6.1 (K), D7.1 (K), D8.1 (K), D9.1 (K), D10.1 (K), D11.1 (K), D12.1 (K), D13.1 (K), D14.1 (K), D15.1 (K), MCU1.22 (PA6)
ROW1: D16.1 (K), D17.1 (K), D18.1 (K), D19.1 (K), D20.1 (K), D21.1 (K), D22.1 (K), D23.1 (K), D24.1 (K), D25.1 (K), D26.1 (K), D27.1 (K), D28.1 (K), D29.1 (K), D30.1 (K), D31.1 (K), MCU1.35 (PB14)
ROW2: D32.1 (K), D33.1 (K), D34.1 (K), D35.1 (K), D36.1 (K), D37.1 (K), D38.1 (K), D39.1 (K), D40.1 (K), D41.1 (K), D42.1 (K), D43.1 (K), D44.1 (K), D45.1 (K), D46.1 (K), D47.1 (K), MCU1.39 (PC8)
ROW3: D48.1 (K), D49.1 (K), D50.1 (K), D51.1 (K), D52.1 (K), D53.1 (K), D54.1 (K), D55.1 (K), D56.1 (K), D57.1 (K), D58.1 (K), D59.1 (K), D60.1 (K), D61.1 (K), D62.1 (K), D63.1 (K), MCU1.36 (PB15)
ROW4: D64.1 (K), D65.1 (K), D66.1 (K), D67.1 (K), D68.1 (K), D69.1 (K), D70.1 (K), D71.1 (K), D72.1 (K), D73.1 (K), D74.1 (K), D75.1 (K), D76.1 (K), D77.1 (K), D78.1 (K), MCU1.24 (PC4)
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
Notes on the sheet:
Buck Converters (5->1v8 & 5->3v3)
USB-C CONN & Shield USB_OTG_HS Controller
SWDebug MCU Reset
Mounting Holes
Mechanical Switches
MCU (STM32F446X) JSTPH CONN 25MHz Crystal
LED Array (WS2812B 2020) Push Switch Rotary Encoder 4-Bit Bidirectional Voltage Level Translator
